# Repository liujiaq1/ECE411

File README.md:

# ECE411

## Team Members:
- Wenhao Cheng [cwenhao@pdx.edu](cwenhao@pdx.edu)
- Blaine R. Jemmett [brj@pdx.edu](brj@pdx.edu)
- Xuening Jia [xuening@pdx.edu](xuening@pdx.edu)
- Jiaqi Liu [liujiaq@pdx.edu](liujiaq@pdx.edu)

## Resources: 
- [ECE 411 Syllabus](http://web.cecs.pdx.edu/~faustm/ece411/syllabus.pdf)
- [ Practicum Project Information and Requirements](http://web.cecs.pdx.edu/~faustm/ece411/homework/PracticumProjectDescription.pdf)

## Meeting Minutes
- [10/17/2019](https://github.com/liujiaq1/ECE411-Team9/blob/master/Meetings/10-17-2019/README.md)

## Parts 
- [Parts List](https://github.com/liujiaq1/ECE411-Team9/blob/master/Parts%20List.xlsx)
- [Datasheets](https://github.com/liujiaq1/ECE411-Team9/blob/master/Datasheets/README.md)

## Homework Documents
- [HW2](https://github.com/liujiaq1/ECE411-Team9/blob/master/HWDocument/ECE411%20HW2.docx)
- [PDS](https://github.com/liujiaq1/ECE411-Team9/blob/master/HWDocument/PDS.pdf)

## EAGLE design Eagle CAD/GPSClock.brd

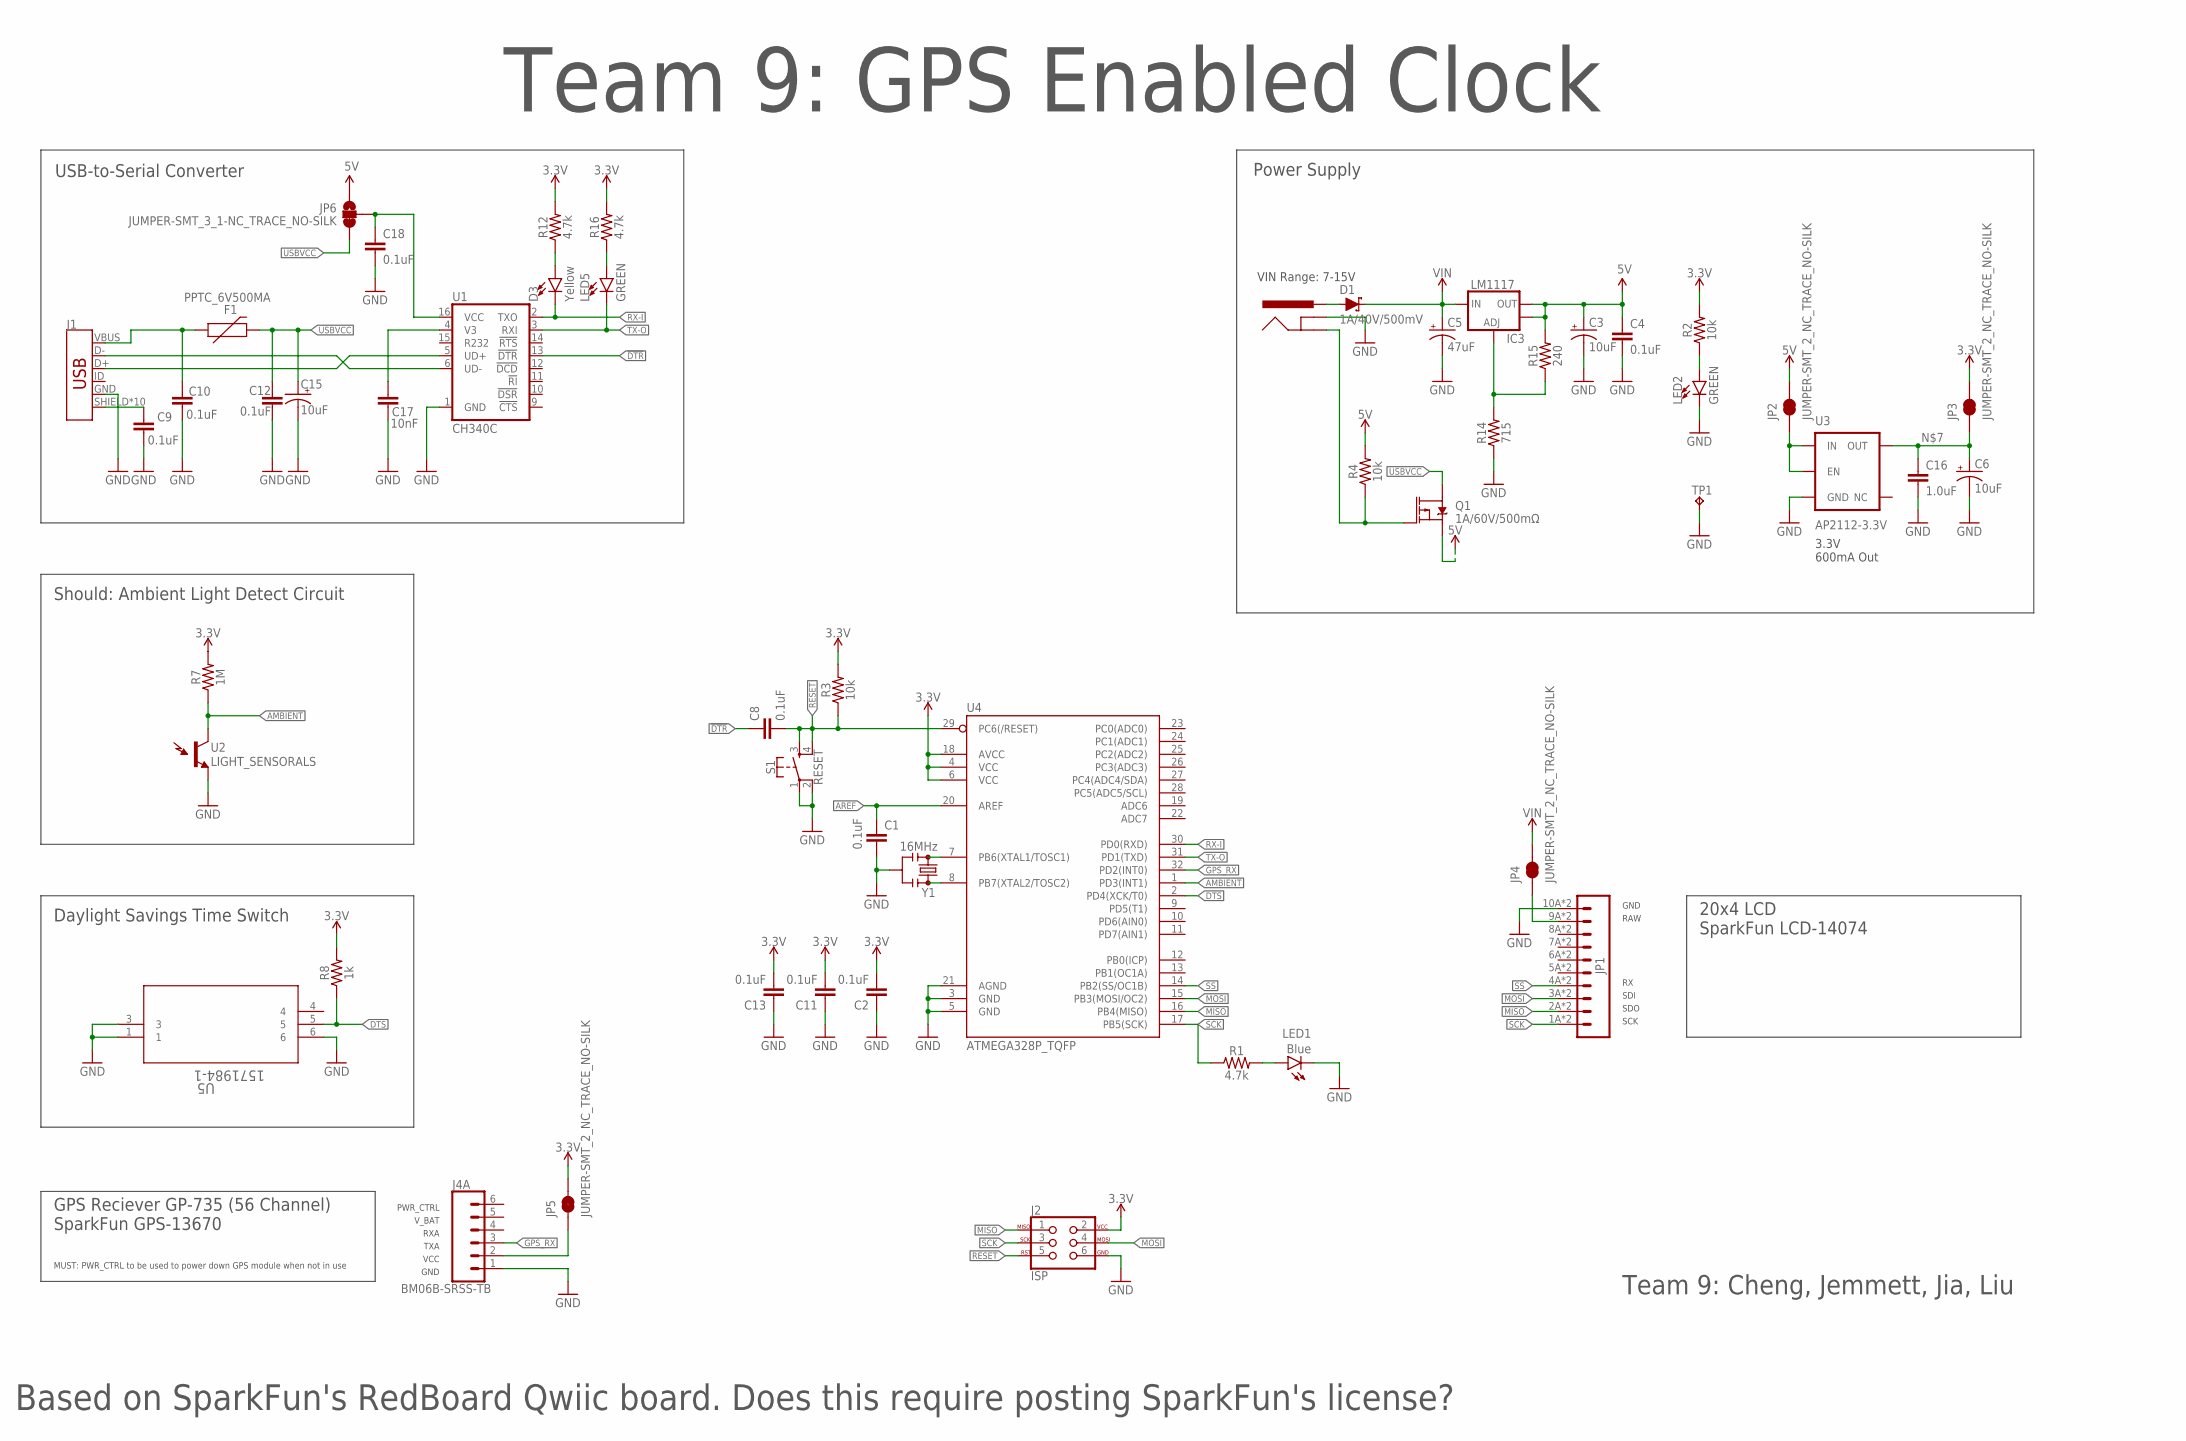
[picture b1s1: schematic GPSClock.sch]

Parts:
C1, C2, C4, C8, C9, C10, C11, C12, C13, C18: 0.1uF; 0603
C3, C6, C15: 10uF; EIA3216
C5: 47uF; PANASONIC_D
C16: 1.0uF; 0603-CAP
C17: 10nF; 0603-CAP
D1: 1A/40V/500mV; SMA-DIODE
D3: Yellow; LED-1206-HIDDENSILK
F1: PPTC_6V500MA; 0805
IC3: LM1117; SOT223-ALT1
J1: AMP FCI 10103594-0001LF; USB-MICROB-PTH-MILL
J2: ISP; 2X3_SMT_POSTS
J3: POWER_JACKSUPER_BOMB_DIGITY; POWER_JACK_SMD_OVERPASTE_SUPER_BOMB_DIGITY
J4: BM06B-SRSS-TB; JST-6-SMD-HORI-1.0MM
JP1: M10SMD_COMBO; 1X10_SMD_COMBINED
JP2, JP3, JP4, JP5: JUMPER-SMT_2_NC_TRACE_NO-SILK; SMT-JUMPER_2_NC_TRACE_NO-SILK
JP6: JUMPER-SMT_3_1-NC_TRACE_NO-SILK; SMT-JUMPER_3_1-NC_TRACE_NO-SILK
LED1: Blue; LED-1206-HIDDENSILK
LED2, LED5: GREEN; LED-1206-HIDDENSILK
Q1: 1A/60V/500mΩ; SOT23-3
R1, R12, R16: 4.7k; 0603
R2, R3, R4: 10k; 0603
R7: 1M; 0603
R8: 1k; 0603
R14: 715; 0603
R15: 240; 0603
S1: RESET; TACTILE_SWITCH_SMD_5.2MM
TP1: TP-063
U1: CH340C; SO016
U2: LIGHT_SENSORALS; ALS-PT19
U3: AP2112-3.3V; SOT23-5
U4: ATMEGA328P_TQFP; TQFP32-08
U5: 1571984-1; SWITCH_1571984-1
Y1: 16MHz; RESONATOR-SMD-3.2X1.3

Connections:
3.3V: C2.2, C11.2, C13.2, J2.2, JP3.2, JP5.2, R2.2, R3.2, R7.2, R8.2, R12.2, R16.2, U4.4 (VCC), U4.6 (VCC), U4.18 (AVCC)
5V: C3.+, C4.1, IC3.2 (OUT), IC3.4 (OUT), JP2.2, JP6.1, Q1.2 (S), R4.2, R15.2
!DTR: C8.1, U1.13 (!DTR)
AMBIENT: R7.1, U2.C (C1), U4.1 (PD3(INT1))
AREF: C1.1, U4.20 (AREF)
DTS: R8.1, U4.2 (PD4(XCK/T0)), U5.5
GND: C1.2, C2.1, C3.-, C4.2, C5.-, C6.-, C9.2, C10.2, C11.1, C12.2, C13.1, C15.-, C16.2, C17.2, C18.2, J1.GND, J2.6, J3.GND (GNDBREAK), J4.1, JP1.10A (10), JP1.10B (10), LED1.C, LED2.C, R14.1, S1.1, S1.2, TP1.1, U1.1 (GND), U2.E (E1), U3.2 (GND), U4.3 (GND), U4.5 (GND), U4.21 (AGND), U5.1, U5.3, U5.6, Y1.2
GPS_RX: J4.3, U4.32 (PD2(INT0))
INSERT: J3.P$4 (GND), Q1.1 (G), R4.1
MISO: J2.1, JP1.2A (2), JP1.2B (2), U4.16 (PB4(MISO))
MOSI: J2.4, JP1.3A (3), JP1.3B (3), U4.15 (PB3(MOSI/OC2))
unnamed: LED1.A, R1.2
unnamed: LED2.A, R2.1
unnamed: U4.7 (PB6(XTAL1/TOSC1)), Y1.1
unnamed: U4.8 (PB7(XTAL2/TOSC2)), Y1.3
unnamed: LED5.A, R16.1
unnamed: C17.1, U1.4 (V3)
unnamed: C6.+, C16.1, JP3.1, U3.5 (OUT)
unnamed: JP2.1, U3.1 (IN), U3.3 (EN)
unnamed: D3.A, R12.1
unnamed: JP1.9A (9), JP1.9B (9), JP4.1
unnamed: J4.2, JP5.1
unnamed: C18.1, JP6.2, U1.16 (VCC)
unnamed: J1.D-, U1.6 (UD-)
unnamed: J1.D+, U1.5 (UD+)
unnamed: IC3.1 (ADJ), R14.2, R15.1
PWRIN: D1.A, J3.VIN0 (PWR)
RESET: C8.2, J2.5, R3.1, S1.3, S1.4, U4.29 (PC6(/RESET))
RX-I: D3.C, U1.2 (TXO), U4.30 (PD0(RXD))
SCK: J2.3, JP1.1A (1), JP1.1B (1), R1.1, U4.17 (PB5(SCK))
SHLD: C9.1, J1.SHIELD, J1.SHIELD2 (SHIELD), J1.SHIELD3 (SHIELD), J1.SHIELD4 (SHIELD), J1.SHIELD5 (SHIELD), J1.SHIELD6 (SHIELD), J1.SHIELD7 (SHIELD), J1.SHIELD8 (SHIELD), J1.SHIELD9 (SHIELD), J1.SHIELD10 (SHIELD)
SS: JP1.4A (4), JP1.4B (4), U4.14 (PB2(SS/OC1B))
TX-O: LED5.C, U1.3 (RXI), U4.31 (PD1(TXD))
USBVCC: C12.1, C15.+, F1.2, JP6.3, Q1.3 (D)
VIN: C5.+, D1.C, IC3.3 (IN), JP4.2
VUSB: C10.1, F1.1, J1.VBUS

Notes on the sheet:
Power Supply
USB-to-Serial Converter
VIN Range: 7-15V
3.3V 600mA Out
Should: Ambient Light Detect Circuit
Team 9: GPS Enabled Clock
Based on SparkFun's RedBoard Qwiic board. Does this require posting SparkFun's license?
GPS Reciever GP-735 (56 Channel) SparkFun GPS-13670
20x4 LCD SparkFun LCD-14074
SDI
SDO
SCK
RAW
GND
VCC
TXA
RXA
V_BAT
PWR_CTRL
MUST: PWR_CTRL to be used to power down GPS module when not in use
Team 9: Cheng, Jemmett, Jia, Liu
Daylight Savings Time Switch

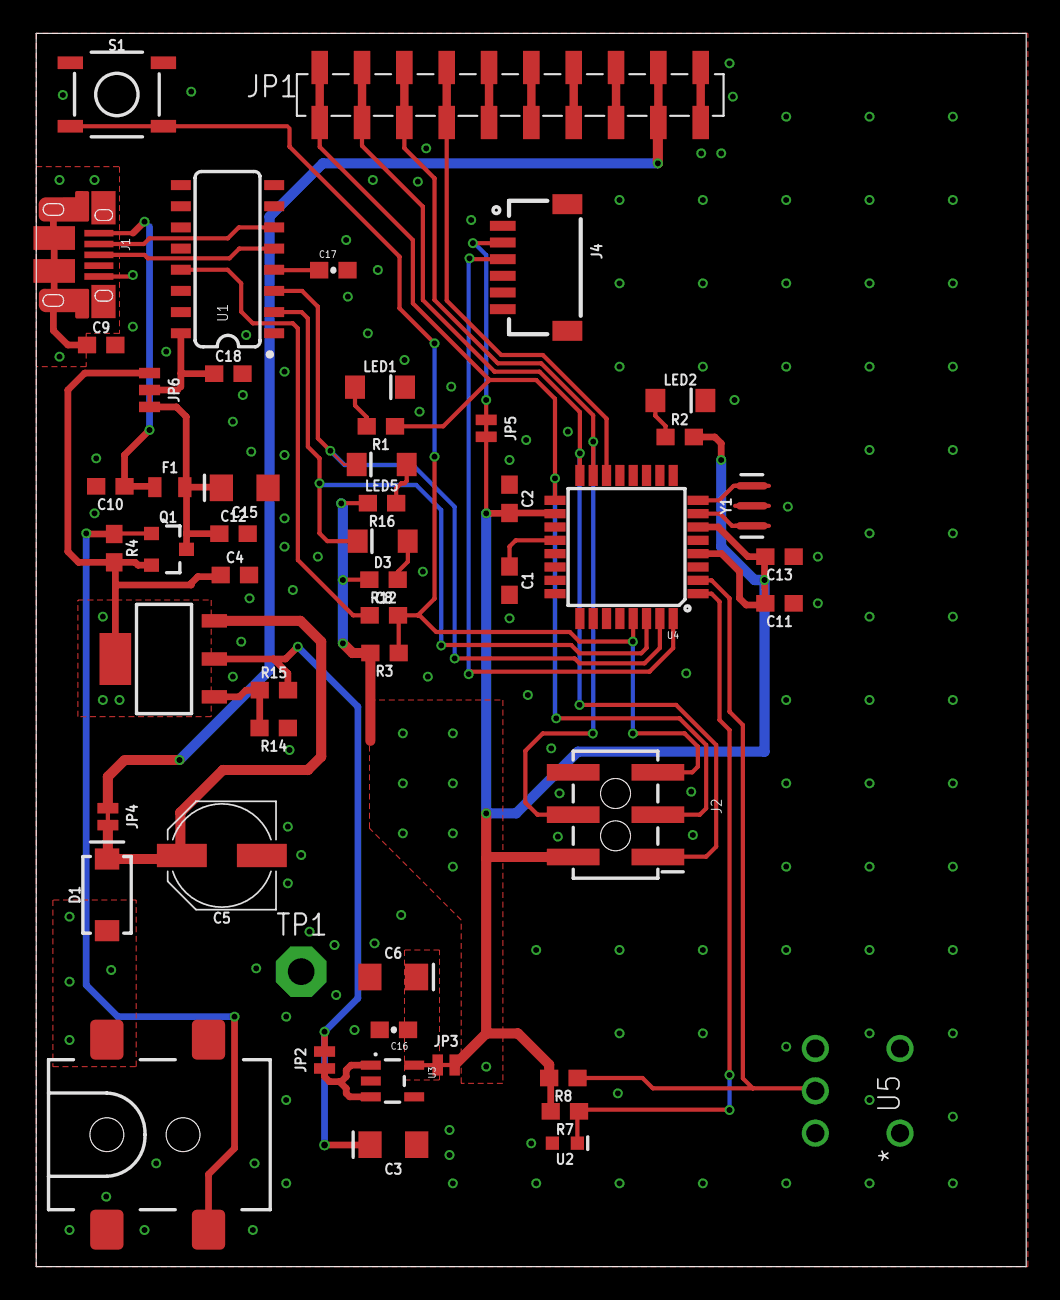
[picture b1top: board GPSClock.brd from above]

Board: 2 copper layers, 59.4 x 74.0 mm, 52 parts (0 on the bottom side), 36 nets.

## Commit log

2019-10-18 Rename Meetings.md to 10-17-2019.md
2019-10-18 Rename Meetings/10-17-2019.md to Meetings/10-17-2019/Minutes.md
2019-10-18 added team and resources
2019-10-18 fixed space issues
2019-10-19 Marked AR Complete
2019-10-19 Rename Minutes.md to README.md
2019-10-19 Corrected AR owner from Jackie to All
2019-10-22 Create HWDocuments
2019-10-22 Create HWDocument
2019-10-22 Update HWDocument
2019-10-31 Add files via upload
    Shows GPS module is transmitting to RedBoard
2019-10-31 updated to show working LCD display
2019-11-05 Updated schematic with correct port for GPS Rx
2019-11-07 updated GPS connection, auto routing for starting point
2019-11-07 updated GPS connector
2019-11-18 Completed List from Eagle BOM
2019-11-18 Updated resonator source and added status column
2019-11-18 Completed OSH Park's DRC
2019-11-18 Fixed board size
    Fixed board size and power connector location to allow for LCD connection
2019-11-19 Added text to BRD.
2019-11-19 Corrected name for OSH Park
2019-11-19 Stitched the N$7 (3.3V) plane
2019-11-20 Added "RESET" to tplace layer
2019-11-20 added "ISP SPI PROG" to tplace layer
2019-11-21 Create notes from other groups
2019-11-21 Create 1
2019-11-21 Create date 12.12(pm1:30-2:00)
2019-12-12 Fixed opening for LCD backlight

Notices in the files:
parts and their libraries:
SparkFun-Capacitors: Licensing: CC v3.0 Share-Alike You are welcome to use this library for commercial purposes.
SparkFun-DiscreteSemi: Licensing: Creative Commons ShareAlike 4.0 International - https://creativecommons.org/licenses/by-sa/4.0
